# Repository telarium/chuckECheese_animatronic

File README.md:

This project is for a retrofit of an old 1981 Cyberanimc Animatronic from Pizza Time Theatre, better known as Chuck E. Cheese's band. A Raspberry Pi was used with a custom circuit board to control the animatronic, adding voice recognition and AI capabilities. Features include:

* Wifi control through an HTML interface
* Voice recognition with wakeword detection
* Speech-to-text support
* Intent detection for pre-defined commands
* Integration with Claude, ChatGPT, or DeepSeek
* Text-to-speech for offline mode or online mode with Elevenlabs for natural sounding speech
* Wireless gamepad support
* Wifi management, including access point mode (hotspot)
* MIDI support for animating new shows

For more detailed information, [read the wiki](https://github.com/telarium/chuckECheese_animatronic/wiki)!

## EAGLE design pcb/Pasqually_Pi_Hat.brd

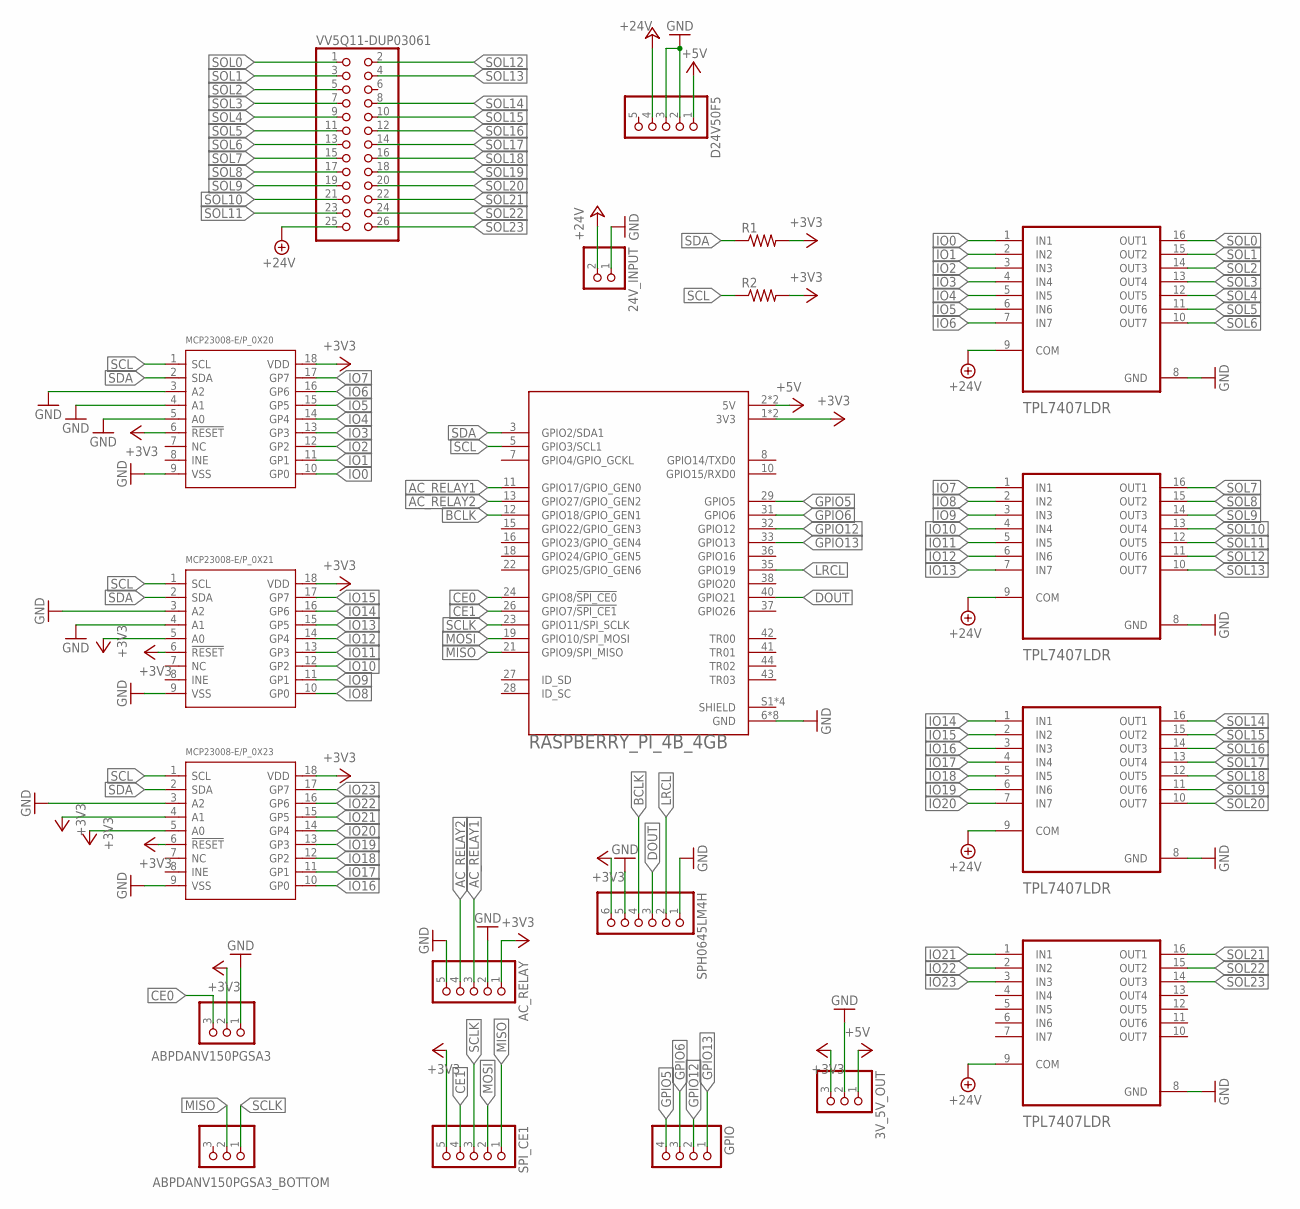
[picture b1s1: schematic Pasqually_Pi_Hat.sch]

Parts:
3V_5V_OUT: PINHD-1X3; 1X03
24V_INPUT: PINHD-1X2; 1X02
ABPDANV150PGSA3, ABPDANV150PGSA3_BOTTOM: PINHD-1X3; 1X03
AC_RELAY: PINHD-1X5; 1X05
D24V50F5: PINHD-1X5; 1X05
GPIO: PINHD-1X4; 1X04
MCP23008-E/P_0X20, MCP23008-E/P_0X21, MCP23008-E/P_0X23: INTERFACE-MCP23008-E/P(DIP18-7.62MM); DIP18-2.54-22.8X7.62MM
R1, R2: R-US_0309/10; 0309/10
SPH0645LM4H: PINHD-1X6; 1X06
SPI_CE1: PINHD-1X5; 1X05
U0, U1, U2, U3: TPL7407LDR; SOIC127P600X175-16N
U4: RASPBERRY_PI_4B_4GB; MODULE_RASPBERRY_PI_4B_4GB
VV5Q11-DUP03061: PINHD-2X13; 2X13

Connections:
+3V3: 3V_5V_OUT.3, ABPDANV150PGSA3.2, AC_RELAY.1, MCP23008-E/P_0X20.6 (!RESET), MCP23008-E/P_0X20.18 (VDD), MCP23008-E/P_0X21.5 (A0), MCP23008-E/P_0X21.6 (!RESET), MCP23008-E/P_0X21.18 (VDD), MCP23008-E/P_0X23.4 (A1), MCP23008-E/P_0X23.5 (A0), MCP23008-E/P_0X23.6 (!RESET), MCP23008-E/P_0X23.18 (VDD), R1.2, R2.2, SPH0645LM4H.6, SPI_CE1.5, U4.1 (3V3), U4.17 (3V3)
+5V: 3V_5V_OUT.1, D24V50F5.1, U4.2 (5V), U4.4 (5V)
+24V: 24V_INPUT.2, D24V50F5.4, U0.9 (COM), U1.9 (COM), U2.9 (COM), U3.9 (COM), VV5Q11-DUP03061.25
AC_RELAY1: AC_RELAY.3, U4.11 (GPIO17/GPIO_GEN0)
AC_RELAY2: AC_RELAY.4, U4.13 (GPIO27/GPIO_GEN2)
BCLK: SPH0645LM4H.4, U4.12 (GPIO18/GPIO_GEN1)
CE0: ABPDANV150PGSA3.3, U4.24 (GPIO8/!SPI_CE0!)
CE1: SPI_CE1.4, U4.26 (GPIO7/!SPI_CE1!)
DOUT: SPH0645LM4H.3, U4.40 (GPIO21)
GND: 3V_5V_OUT.2, 24V_INPUT.1, ABPDANV150PGSA3.1, AC_RELAY.2, AC_RELAY.5, D24V50F5.2, D24V50F5.3, MCP23008-E/P_0X20.3 (A2), MCP23008-E/P_0X20.4 (A1), MCP23008-E/P_0X20.5 (A0), MCP23008-E/P_0X20.9 (VSS), MCP23008-E/P_0X21.3 (A2), MCP23008-E/P_0X21.4 (A1), MCP23008-E/P_0X21.9 (VSS), MCP23008-E/P_0X23.3 (A2), MCP23008-E/P_0X23.9 (VSS), SPH0645LM4H.1, SPH0645LM4H.5, U0.8 (GND), U1.8 (GND), U2.8 (GND), U3.8 (GND), U4.6 (GND), U4.9 (GND), U4.14 (GND), U4.20 (GND), U4.25 (GND), U4.30 (GND), U4.34 (GND), U4.39 (GND)
GPIO5: GPIO.4, U4.29 (GPIO5)
GPIO6: GPIO.3, U4.31 (GPIO6)
GPIO12: GPIO.2, U4.32 (GPIO12)
GPIO13: GPIO.1, U4.33 (GPIO13)
IO0: MCP23008-E/P_0X20.10 (GP0), U0.1 (IN1)
IO1: MCP23008-E/P_0X20.11 (GP1), U0.2 (IN2)
IO2: MCP23008-E/P_0X20.12 (GP2), U0.3 (IN3)
IO3: MCP23008-E/P_0X20.13 (GP3), U0.4 (IN4)
IO4: MCP23008-E/P_0X20.14 (GP4), U0.5 (IN5)
IO5: MCP23008-E/P_0X20.15 (GP5), U0.6 (IN6)
IO6: MCP23008-E/P_0X20.16 (GP6), U0.7 (IN7)
IO7: MCP23008-E/P_0X20.17 (GP7), U1.1 (IN1)
IO8: MCP23008-E/P_0X21.10 (GP0), U1.2 (IN2)
IO9: MCP23008-E/P_0X21.11 (GP1), U1.3 (IN3)
IO10: MCP23008-E/P_0X21.12 (GP2), U1.4 (IN4)
IO11: MCP23008-E/P_0X21.13 (GP3), U1.5 (IN5)
IO12: MCP23008-E/P_0X21.14 (GP4), U1.6 (IN6)
IO13: MCP23008-E/P_0X21.15 (GP5), U1.7 (IN7)
IO14: MCP23008-E/P_0X21.16 (GP6), U2.1 (IN1)
IO15: MCP23008-E/P_0X21.17 (GP7), U2.2 (IN2)
IO16: MCP23008-E/P_0X23.10 (GP0), U2.3 (IN3)
IO17: MCP23008-E/P_0X23.11 (GP1), U2.4 (IN4)
IO18: MCP23008-E/P_0X23.12 (GP2), U2.5 (IN5)
IO19: MCP23008-E/P_0X23.13 (GP3), U2.6 (IN6)
IO20: MCP23008-E/P_0X23.14 (GP4), U2.7 (IN7)
IO21: MCP23008-E/P_0X23.15 (GP5), U3.1 (IN1)
IO22: MCP23008-E/P_0X23.16 (GP6), U3.2 (IN2)
IO23: MCP23008-E/P_0X23.17 (GP7), U3.3 (IN3)
LRCL: SPH0645LM4H.2, U4.35 (GPIO19)
MISO: ABPDANV150PGSA3_BOTTOM.2, SPI_CE1.1, U4.21 (GPIO9/SPI_MISO)
MOSI: SPI_CE1.2, U4.19 (GPIO10/SPI_MOSI)
SCL: MCP23008-E/P_0X20.1 (SCL), MCP23008-E/P_0X21.1 (SCL), MCP23008-E/P_0X23.1 (SCL), R2.1, U4.5 (GPIO3/SCL1)
SCLK: ABPDANV150PGSA3_BOTTOM.1, SPI_CE1.3, U4.23 (GPIO11/SPI_SCLK)
SDA: MCP23008-E/P_0X20.2 (SDA), MCP23008-E/P_0X21.2 (SDA), MCP23008-E/P_0X23.2 (SDA), R1.1, U4.3 (GPIO2/SDA1)
SHIELD: U4.S1 (SHIELD), U4.S2 (SHIELD), U4.S3 (SHIELD), U4.S4 (SHIELD)
SOL0: U0.16 (OUT1), VV5Q11-DUP03061.1
SOL1: U0.15 (OUT2), VV5Q11-DUP03061.3
SOL2: U0.14 (OUT3), VV5Q11-DUP03061.5
SOL3: U0.13 (OUT4), VV5Q11-DUP03061.7
SOL4: U0.12 (OUT5), VV5Q11-DUP03061.9
SOL5: U0.11 (OUT6), VV5Q11-DUP03061.11
SOL6: U0.10 (OUT7), VV5Q11-DUP03061.13
SOL7: U1.16 (OUT1), VV5Q11-DUP03061.15
SOL8: U1.15 (OUT2), VV5Q11-DUP03061.17
SOL9: U1.14 (OUT3), VV5Q11-DUP03061.19
SOL10: U1.13 (OUT4), VV5Q11-DUP03061.21
SOL11: U1.12 (OUT5), VV5Q11-DUP03061.23
SOL12: U1.11 (OUT6), VV5Q11-DUP03061.2
SOL13: U1.10 (OUT7), VV5Q11-DUP03061.4
SOL14: U2.16 (OUT1), VV5Q11-DUP03061.8
SOL15: U2.15 (OUT2), VV5Q11-DUP03061.10
SOL16: U2.14 (OUT3), VV5Q11-DUP03061.12
SOL17: U2.13 (OUT4), VV5Q11-DUP03061.14
SOL18: U2.12 (OUT5), VV5Q11-DUP03061.16
SOL19: U2.11 (OUT6), VV5Q11-DUP03061.18
SOL20: U2.10 (OUT7), VV5Q11-DUP03061.20
SOL21: U3.16 (OUT1), VV5Q11-DUP03061.22
SOL22: U3.15 (OUT2), VV5Q11-DUP03061.24
SOL23: U3.14 (OUT3), VV5Q11-DUP03061.26

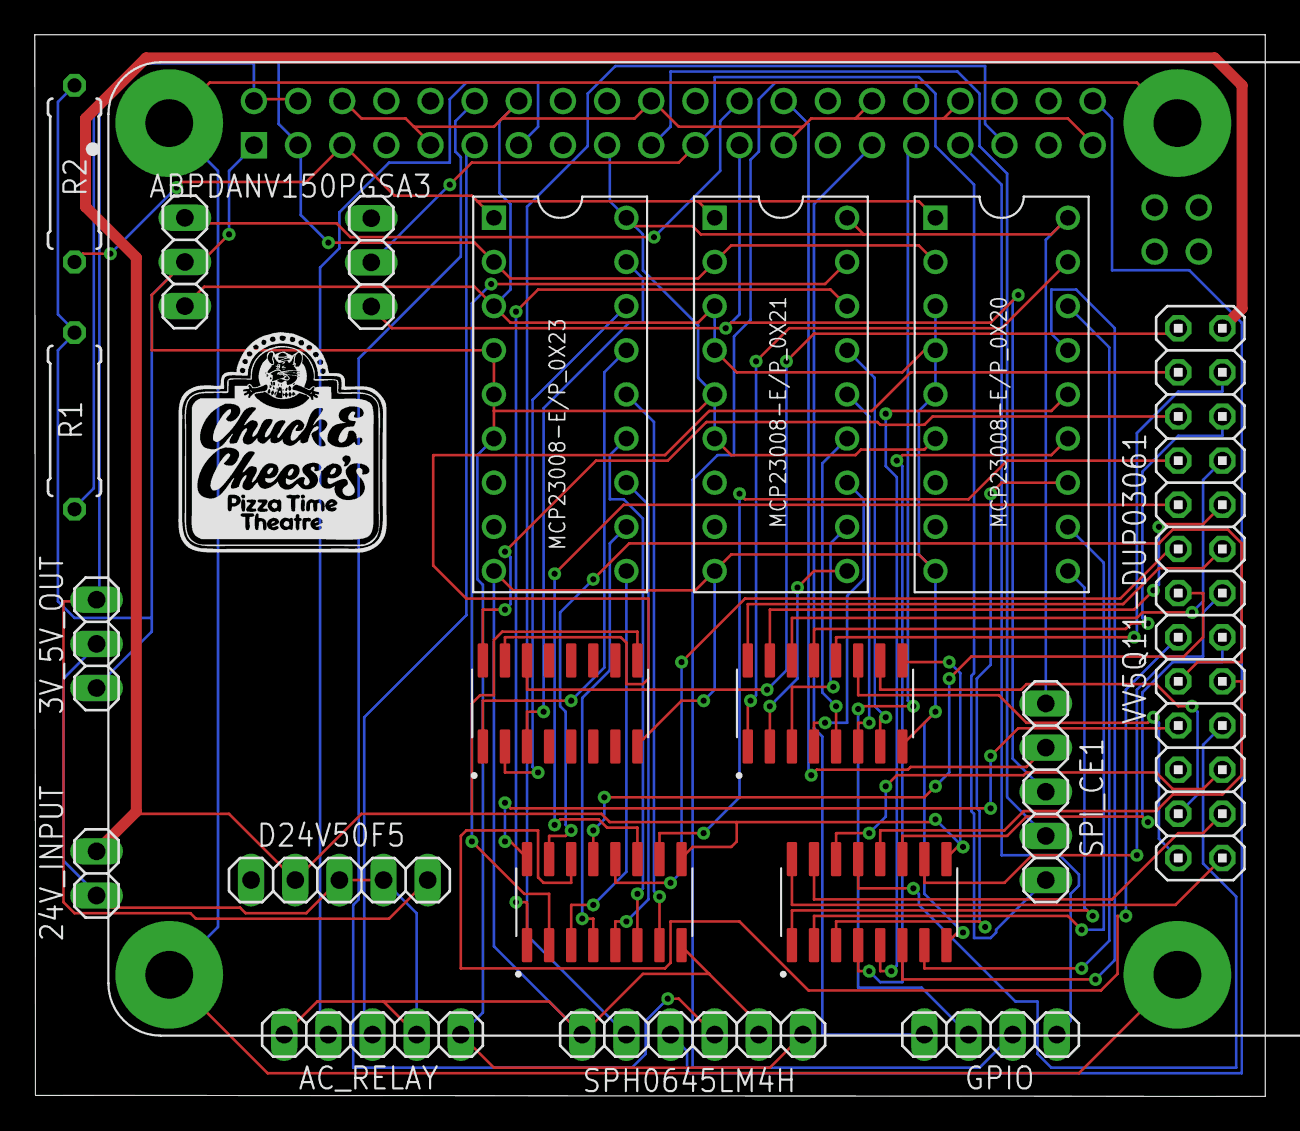
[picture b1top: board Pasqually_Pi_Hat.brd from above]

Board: 2 copper layers, 70.8 x 61.1 mm, 20 parts (0 on the bottom side), 69 nets.

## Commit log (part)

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2016-01-30 Fixes
2016-02-07 Devy
2016-02-23 More dev
2016-02-28 Added AJAX key press functionality
2016-02-29 Global function call added
2016-03-01 Fixed keypresses
2016-03-02 More IO functionality
2016-03-02 Added IO
2016-03-02 Fixed key down event
2016-03-02 Added libsoc package
2016-03-02 Added more debs
2016-03-02 Implemented libsoc for GPIO
2016-03-03 Finished first pass implemenetion with libsoc
2016-03-07 Began adding getMidi functions
2016-03-09 Removing bad merge crap
2016-03-09 Bo Diddley
2016-03-09 Added MIDI stuff in javascript
2016-12-27 Added comments about pinout
2016-12-27 Added
2016-12-27 Bug fixes
2017-01-11 Start web server on port 80
2017-01-29 Swapping libsoc for CHIP_IO
2017-01-31 Fixed CHIP gpio implementation
2017-01-31 Debuggin
2017-02-08 Cleaning up setup scripts
2017-03-03 Added movement id's
2017-03-03 Tweaked movements
2017-04-04 Fixed link movement issue
2017-04-05 Added threading
2017-05-07 Added max pin time functionality
2017-05-08 Starting service in threaded mode in an attempt to solve slowdown issues
2017-05-08 Properly setting outputpin2 on startup. Also swapping arm pins
2017-05-09 Threaded mess
2017-05-31 Added dispatch and callback functionality
2017-05-31 Removed old variables
2017-06-28 Implemented dispatch events and fixed callback function for eyes
2017-06-29 Switched Ajax with SocketIO
2017-07-05 Added new website design and folder structure
2017-07-09 Fixed video playback and added socketio communication
2017-07-19 Web fixes and added eye movement
2017-07-21 Added system update calls
2017-07-21 Added webcam support
2017-07-22 Fixed webcam functionality
2017-07-23 Added keypad graphic, network manager support, and MIDI output events
2017-07-24 Added web gamepad support
2017-07-24 Fixed scoping error
2017-07-26 Video now seamlessly looped
2017-07-27 Added note about MIDI loopback software
2017-08-09 Added bare bones midi output functionality... work in progress
2017-08-10 Cleanded up MIDI out code
2017-08-11 Better MIDI event handling
2017-08-11 Better wifi scanning data
2017-12-11 Added setup fixes
2017-12-11 Added Flask upload and better event support
2018-01-23 Renamed
2024-09-05 Well hello, old friend.
    Porting code to Python3 and to work on the Raspberry Pi. Lots of other bug fixes.
2024-09-07 Support for GPIO with the MCP23008
2024-09-08 Added support for a USB MIDI interface
2024-09-13 Debugging MIDI results
2024-09-29 Updating comments to reflect new IO/solenoid assignments
2024-09-29 Restoring web MIDI output/input, enabling HTTPS server in order to support MIDI events in newer browser versions
2024-09-29 Correct pins now assigned to each movement... theoretically.
2024-09-29 Added PCB schematics for the new Raspberry Pi hat to control the solenoid bank and other sensors
2024-09-29 Setting correct i2c addresses based on the Raspberry Pi hat schematic, based on how pins A0, A1, and A2 are connected
2024-09-29 Update README.md
    It's no longer a CHIP project, sadly. Next Thing Co went out of business years ago, so now it's a Raspberry Pi project.
2024-10-14 Updating setup script
2024-10-14 Testing movements and fixing incorrect IO assignment
2024-10-14 Added right keypad image, adjusted left one. WIP.
2024-10-16 Removed MIDI class (will be handled through web MIDI instead), and added early USB gamepad support
2024-10-18 Fixed issued where simultaneous key events were sometimes ignored
2024-10-18 Some refinements and optimizations
2024-10-18 Experimenting with a higher update interval
2024-10-18 Mapping analog sticks to a dpad value. Not implemented very well at the moment.
2024-10-18 More horrible gamepad code
2024-10-20 Better support for linked keys
2024-10-20 Full gamepad support for all movements (except body lean)
2024-10-20 Asked AI to clean this up and simplify it. Because I'm lazy and tired of gamepad programming
2024-10-20 Assigned MIDI notes to linked movements, plus some cleanup and name changing
2024-10-21 Refining MIDI control. But might swap to use RTP MIDI instead
2024-10-23 Early mirrored support
2024-10-23 Alternate implementation of mirrored mode
2024-10-24 Adding ability to toggle mirrored mode with gamepad. Or in the future, web socket events
2024-11-27 Modified MIDI support for LoopBe30 instead. Added first version of MIDI/MP3/Wave/OGG playback with animation data
2024-12-01 First implementation of the HTML being able to select a show from the list. Also first implementation of audio playback with pause and stop functionality.
2024-12-27 Starting VoiceControl functionality
2025-01-02 First pass at voice control with ChatGPT and other technologies
2025-01-02 Tweaking how silence is handled for the end of utterance
2025-01-06 Tweaked max output times, how the gamepad controls the neck
2025-01-06 Better support for show playback with events
2025-01-06 (Almost) full support for Porcupine, Rhino, Google speech-to-text, and ChatGPT
2025-01-07 Added Elevenlabs support for text to speech
2025-01-07 Further refinements for silence detection, less spam, more fun!
2025-01-07 Changed monkey_patch parameters that kept the voice control class from using arecord properly for some reason.
2025-01-07 More graceful handling of shutdown
2025-01-13 Fleshed out voice commands, added fancy audio
2025-01-13 Implemented automated puppeting class
2025-01-13 Increased sample rate of tts
2025-01-13 Fixed formatting. Added MP3 support
2025-01-13 Removed function to convert tts mp3 to wav. No longer necessary
2025-01-14 Cleaned up audio, replaced some OGG files with WAV due to them being less laggy
2025-01-14 Added lots of error handling for voice/AI implementation
2025-01-14 Refined ChatGPT context
2025-01-14 More error handling for when Porcupine wakeword has not been correctly set up
2025-01-15 HTML cleanup
2025-01-15 CSS cleanup, fixing image width issues with keypad graphics
2025-01-15 Added "retro mode" functionality. Also added HTML checkboxes for retro mode and mirrored mode
2025-01-16 Handle cases where a microphone is not present
2025-01-16 Using Piper fopr TTS fallback if Elevenlabs not available. Replaces pico2wave, which is... rough sounding.
2025-01-17 Formatting cleanup
2025-01-17 Added ability for web frontend to display voice command status
2025-01-17 Adding TTS text input from web frontend
2025-01-17 More web formatting tweaks
2025-01-17 Cleaned up unused styling
2025-01-18 Ability to restore previous voice command to display on web frontend
2025-01-19 Improving Pasqually's voice
2025-01-19 Removed unecessary return... I think?
2025-01-19 Moved this event id to Python
2025-01-19 Added random idle animations while Pasqually is processing voice commands
2025-01-19 Tweaking existing wifi management, beginning to add new wifi management features
2025-01-20 Switched to using pywifi... because why reinvent the wheel?
2025-01-20 Added web front-end support to scan and connect to wifi networks.
2025-01-21 Minor layout tweaks
2025-01-21 Stop any active show when a wakeword is detected
2025-01-21 Add ability to play a song at random
2025-01-21 Added new Rhino command. Implemented the ability to play a random song
2025-01-21 Quick fix for hotspot deactivation
2025-01-21 Remove special fonts. Use regular fonts.
2025-01-22 Make hotspot audio play sooner
2025-01-22 Formatting fixes. Don't display keypad sections on mobile devices
2025-01-22 Changed wifi scanning function to not use PiWifi, which has some problems with AP mode
2025-01-22 Style improvements
2025-01-22 Cleaned and optimized javascript
2025-01-22 Fixed video banner formatting
2025-01-22 Refactored how system info is communicated
2025-01-22 Cache wifi scan results. We can re-use them since wifi scanning isn't allowed in AP mode
2025-01-22 Use tts for reading the wifi network out loud
2025-01-23 Added hotspot status and activating/deactivating from web frontend
2025-01-24 Added support for DeepSeek as an alternative to ChatGPT
2025-01-24 Config support for deepseek API key
2025-02-05 Removed Flask Uploads dependency. For now.
2025-02-05 Make sure hostapd is unmaked when starting an access point
2025-02-05 Fail gracefully if the GPIO IC chips are not present
2025-02-05 Fixed bad directory for Piper TTS voice download
2025-02-05 Added support for the ABPDANV150PGSA3 air pressure sensor
2025-02-05 Tweaked parameteres for better automatic mouth puppeting
2025-02-05 Tweaking random times for automatic left/right eye movements and blinks
2025-02-05 Calibrating the PSI to match real-world results
2025-02-05 Fixed issue with the animation drifting out of sync with the audio over time.
2025-02-05 Added support for reading air pressure value out loud
2025-02-12 Gamepad events now output MIDI values again
2025-02-13 Set wlan1 to use the same SSID as wlan0... if wlan1 exists
2025-02-13 Added better error messaging
2025-02-13 Better error log messaging
2025-02-13 Added support for inverting head up/down (nod) motion
2025-02-13 Fixed MIDI port detection. Added support for inverting head nod movements
2025-02-13 Added support for inverted head nod checkbox
2025-02-13 Removed some console logs I was using for debugging
2025-02-13 Various tweaks and bug fixes. Added support to reset to a defaul animation state.
2025-02-13 Tweaked wifi scanning functionality, added support for default animation poses, various bug fixes
2025-02-13 Tweaked wifi scanning functionality
2025-02-13 Dispatch event when a show has ended
2025-02-17 Removed eventlet and substituted with standard threading. Eventlet seemed to be getting too laggy
2025-02-17 Fixed a really dumb copy+paste bug
2025-02-17 Changed threading so it can all shut down without spewing errors
2025-02-17 Added some new basic commands
2025-02-17 Supress annoyhing Pygame messages
2025-02-17 Removed debug message
2025-02-17 Added optional flag to save TTS audio instead of discarding them in a temp dir
2025-03-10 Made adjustements to some functionality now that threading is simplified. Refined idle animations.
2025-03-10 Re-added body lean movement. Some new idle animation work, and refining threads now that eventlet is gone
2025-03-10 Changed how threading works
2025-03-10 Added head look up/down command
2025-03-10 Tweaked some status settings
2025-03-10 Removed HTTPS support, cleaned up old code, use new threading methods
2025-03-10 Tweaked keyboard graphics
2025-03-10 Code cleanup
2025-03-10 Added MIDI port class
2025-03-10 New fun audio commands
2025-03-15 Removing debug messages
2025-04-07 Code cleanup and show added!
2025-04-07 Restore clean config.cfg from master
2025-04-07 Update LICENSE
2025-04-25 Added a bunch of vocal samples from original Pasqually recordings
2025-04-26 Fixed bug with intents not playing successfully, making config file paths work with Linux systemd services
2025-04-26 Fixed bug with server not starting from systemd service
2025-04-26 Fix config path when running from systemd service
2025-10-28 Added 'say' command to repeat back what was said.
2026-06-21 Added Claude support
2026-06-21 Updated to mention Claude
2026-06-21 Updated to add Claude support

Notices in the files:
pcb/Pasqually_Pi_Hat.brd:
©2025 LangleyCreations
